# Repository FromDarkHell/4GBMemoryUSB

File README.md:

# 4GBMemoryUSB

This is a USB dongle for connecting an Xbox 360 4GB Internal Memory Module to your PC.
These modules are basically a complete USB implementation, but with a 3.3V VCC rather than 5V (which is standard for USB). So, this board is just a USB plug, alongside a voltage regulator to go from 5V to 3.3V.

Additionally, you'll need to pull the memory module socket from your Trinity xbox.

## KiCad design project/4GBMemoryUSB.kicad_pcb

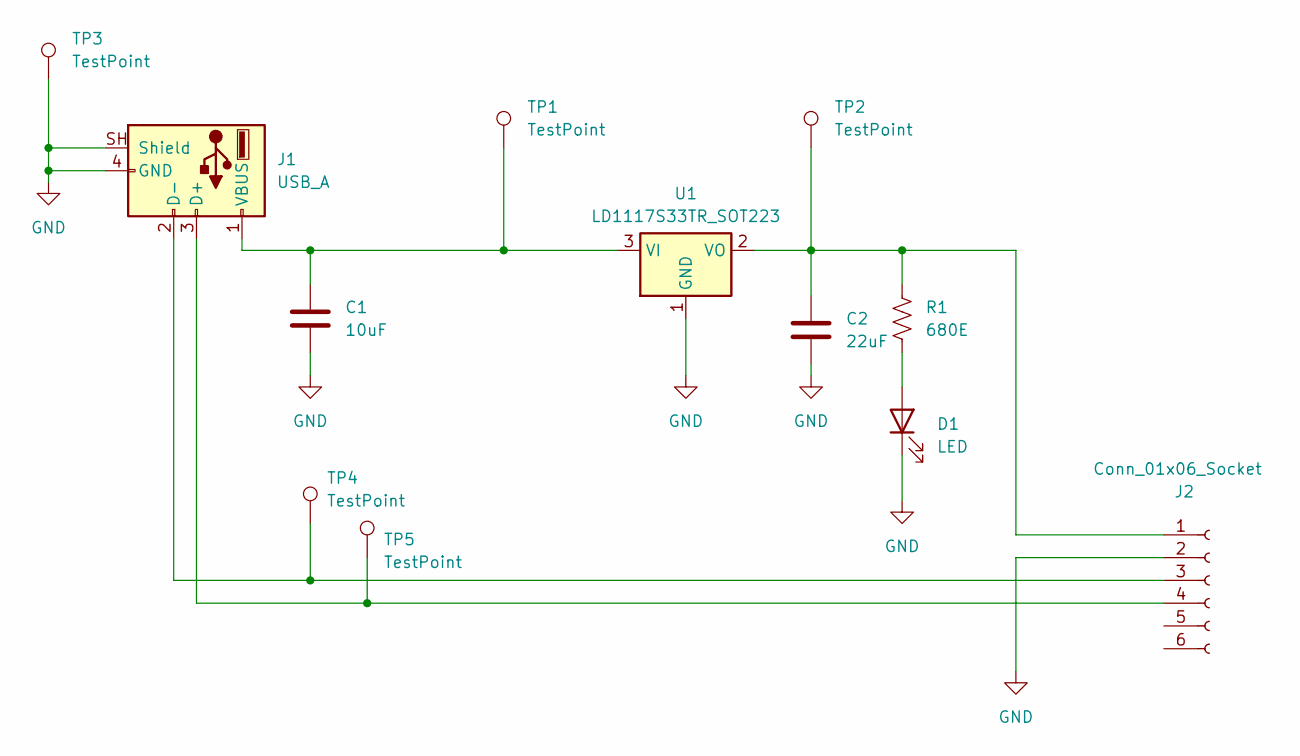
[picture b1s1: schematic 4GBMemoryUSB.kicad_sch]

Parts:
C1: 10uF; C_0603_1608Metric_Pad1.08x0.95mm_HandSolder
C2: 22uF; C_0603_1608Metric_Pad1.08x0.95mm_HandSolder
D1: LED; LED_0603_1608Metric_Pad1.05x0.95mm_HandSolder
J1: USB_A; USB_A_Molex_48037-2200_Horizontal
J2: Conn_01x06_Socket; MemoryUnitConnector
R1: 680E; R_0603_1608Metric_Pad0.98x0.95mm_HandSolder
TP1, TP2, TP3, TP4, TP5: TestPoint; TestPoint_Pad_D2.0mm
U1: LD1117S33TR_SOT223; SOT-223-3_TabPin2

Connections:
GND: C1.2, C2.2, D1.1 (K), J1.4 (GND), J1.SH (Shield), J2.2, TP3.1 (1_1), U1.1 (GND)
unnamed: D1.2 (A), R1.2
unnamed: J1.3 (D+), J2.4, TP5.1 (1_1)
unnamed: J1.2 (D-), J2.3, TP4.1 (1_1)
unnamed: C1.1, J1.1 (VBUS), TP1.1 (1_1), U1.3 (VI)
unnamed: C2.1, J2.1, R1.1, TP2.1 (1_1), U1.2 (VO)

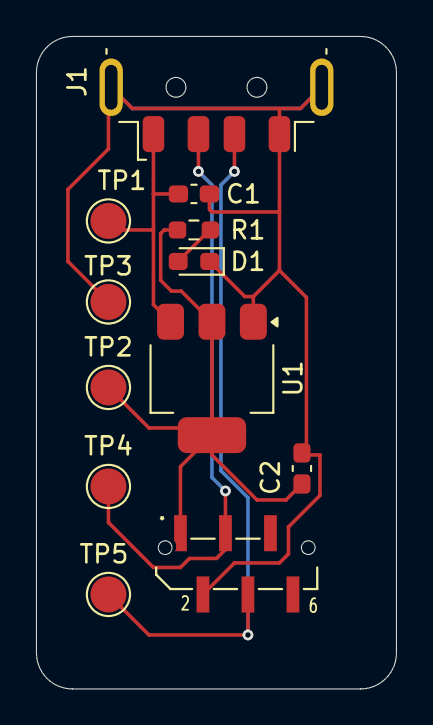
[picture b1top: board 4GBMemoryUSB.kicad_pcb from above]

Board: 2 copper layers, 20.0 x 36.2 mm, 12 parts (0 on the bottom side), 6 nets.
